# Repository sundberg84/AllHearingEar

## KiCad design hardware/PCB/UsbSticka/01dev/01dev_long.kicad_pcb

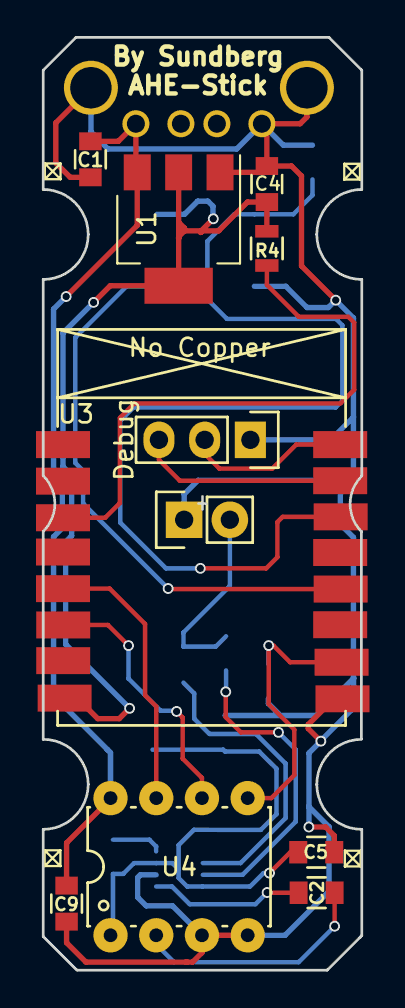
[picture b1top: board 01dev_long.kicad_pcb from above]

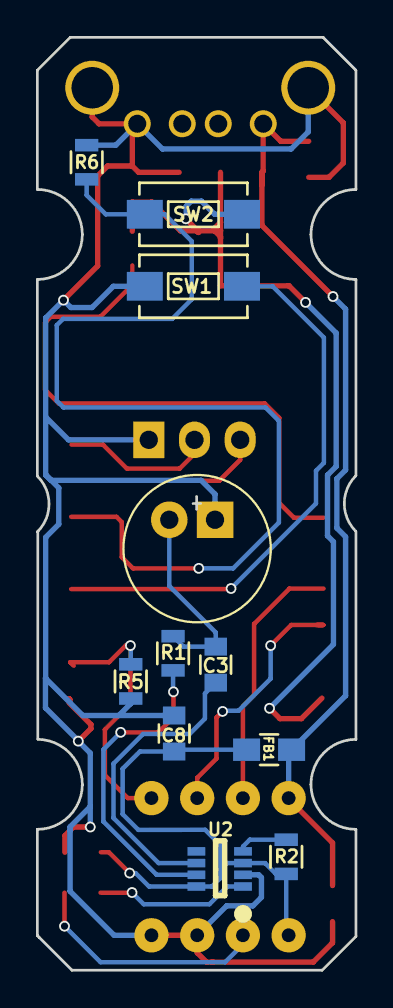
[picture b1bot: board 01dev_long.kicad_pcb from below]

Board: 2 copper layers, 17.7 x 51.8 mm, 22 parts (10 on the bottom side), 18 nets.

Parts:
C1, C2, C3, C5, C8, C9: 0,1; C_0805
C4: 10; C_0805
Debug: Debug; Socket_Strip_Straight_1x03
FB1: FERRITE; C_0805_HandSoldering
P1: USB_B; USB_A_AS
P2: MIC; Socket_Strip_Straight_1x02
R1, R2: 2,2k; R_0805
R4, R5, R6: 10k; R_0805
SW1, SW2: SW_PUSH; SW_SPST_EVQPE1
U1: LM1117-3.3; SOT-223
U2: MAX9813; SOT-23-8
U3: ESP-07v2; ESP-07_AS
U4: MCP3201; PDIP-8

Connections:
+5V: C1.1, C9.2, FB1.2, P1.1, U1.3, U4.8
ANALOG: C2.2, U4.2
GND: C1.2, C4.2, C5.1, C8.1, C9.1, Debug.1, P1.4, P1.5, P2.1, R5.2, R6.1, SW1.2, U1.1, U2.2, U3.9, U4.3, U4.4
MISO: U3.6, U4.6
unnamed: C2.1, U2.1
unnamed: C3.1, P2.2, R1.2
unnamed: C3.2, U2.6
unnamed: C5.2, C8.2, FB1.1, R2.1, U2.3, U2.8, U4.1
unnamed: Debug.2, U3.16
unnamed: Debug.3, U3.15
unnamed: R1.1, U2.7
unnamed: R2.2, U2.4
unnamed: R4.1, U3.3
unnamed: R6.2, SW2.1, U3.14
unnamed: SW1.1, U3.12
SCLK: U3.5, U4.7
SS: R5.1, U3.10, U4.5
VCC: C4.1, R4.2, SW2.2, U1.2, U1.4, U3.8

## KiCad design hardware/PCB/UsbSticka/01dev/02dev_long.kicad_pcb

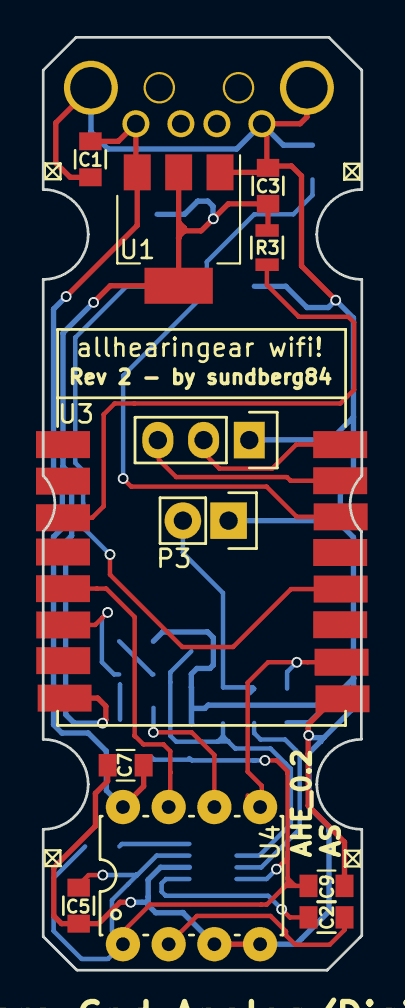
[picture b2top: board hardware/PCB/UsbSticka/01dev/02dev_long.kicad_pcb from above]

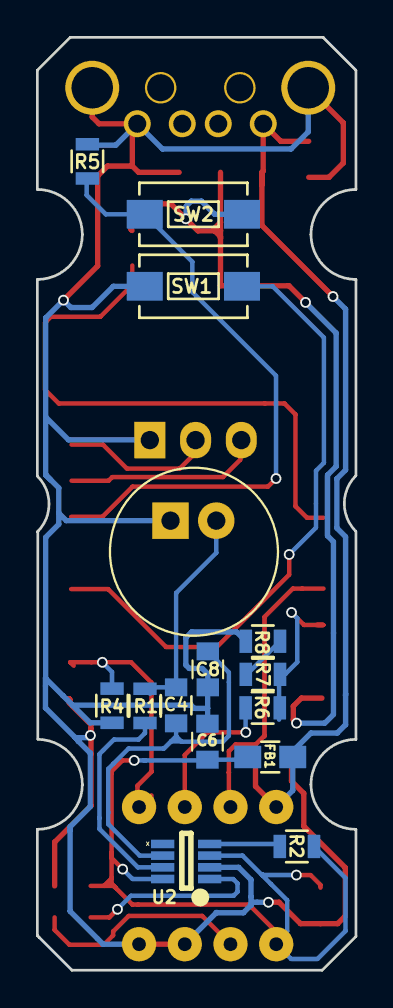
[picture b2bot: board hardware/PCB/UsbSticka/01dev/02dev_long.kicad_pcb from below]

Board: 2 copper layers, 17.7 x 51.8 mm, 27 parts (14 on the bottom side), 20 nets.

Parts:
C1, C2, C4, C5, C6, C7, C8: 0,1; C_0805
C3: 10; C_0805
C9: 10uF; C_0805
FB1: FERRITE; C_0805_HandSoldering
P1: USB_B; USB_A_AS
P2: MIC; Socket_Strip_Straight_1x02
P3: Debug; Socket_Strip_Straight_1x03
R1, R2: 2,2k; R_0805
R3, R4, R5: 10k; R_0805
R6, R7, R8: 1k; R_0805
SW1, SW2: SW_PUSH; SW_SPST_EVQPE1
U1: LM1117-3.3; SOT-223
U2: MAX9813; SOT-23-8
U3: ESP-07v2; ESP-07_AS
U4: MCP3201; PDIP-8

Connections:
+5V: C1.1, C7.2, FB1.2, P1.1, U1.3, U4.8
ANALOG: C2.1, U2.1
GND: C1.2, C3.2, C5.1, C6.1, C7.1, C8.1, C9.2, P1.4, P1.5, P2.1, P3.1, R4.2, R5.1, R8.2, SW1.2, U1.1, U2.2, U3.9, U4.3, U4.4
MISO: R6.1, R7.1, U3.6
unnamed: C2.2, U4.2
unnamed: C4.1, P2.2, R1.2
unnamed: C4.2, C8.2, U2.6
unnamed: C5.2, C6.2, C9.1, FB1.1, R2.1, U2.3, U2.8, U4.1
unnamed: P3.2, U3.16
unnamed: P3.3, U3.15
unnamed: R1.1, U2.7
unnamed: R2.2, U2.4
unnamed: R3.1, U3.3
unnamed: R5.2, SW2.1, U3.14
unnamed: R6.2, U4.6
unnamed: R7.2, R8.1
unnamed: SW1.1, U3.12
SCLK: U3.5, U4.7
SS: R4.1, U3.10, U4.5
VCC: C3.1, R3.2, SW2.2, U1.2, U1.4, U3.8

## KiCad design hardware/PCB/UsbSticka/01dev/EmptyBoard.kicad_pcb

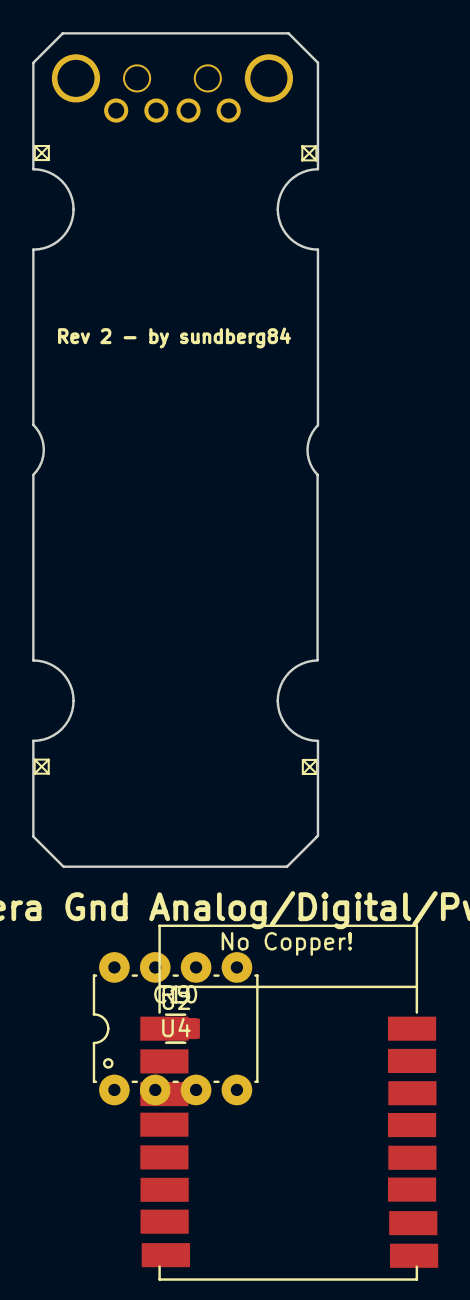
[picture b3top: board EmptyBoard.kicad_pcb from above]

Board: 2 copper layers, 17.7 x 51.8 mm, 5 parts (0 on the bottom side), 6 nets.

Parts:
C10: 0,1; C_0805
P1: USB_B; USB_A_AS
R9: 10k; R_0805
U2: ESP-07v2; ESP-07_AS
U4: MCP3201; PDIP-8

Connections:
GND: C10.1, P1.4, P1.5, R9.2, U2.9, U4.3, U4.4
MISO: U2.6, U4.6
unnamed: C10.2, U4.1
SCLK: U2.5, U4.7
SS: U2.10, U4.5
VCC: U2.8, U4.8

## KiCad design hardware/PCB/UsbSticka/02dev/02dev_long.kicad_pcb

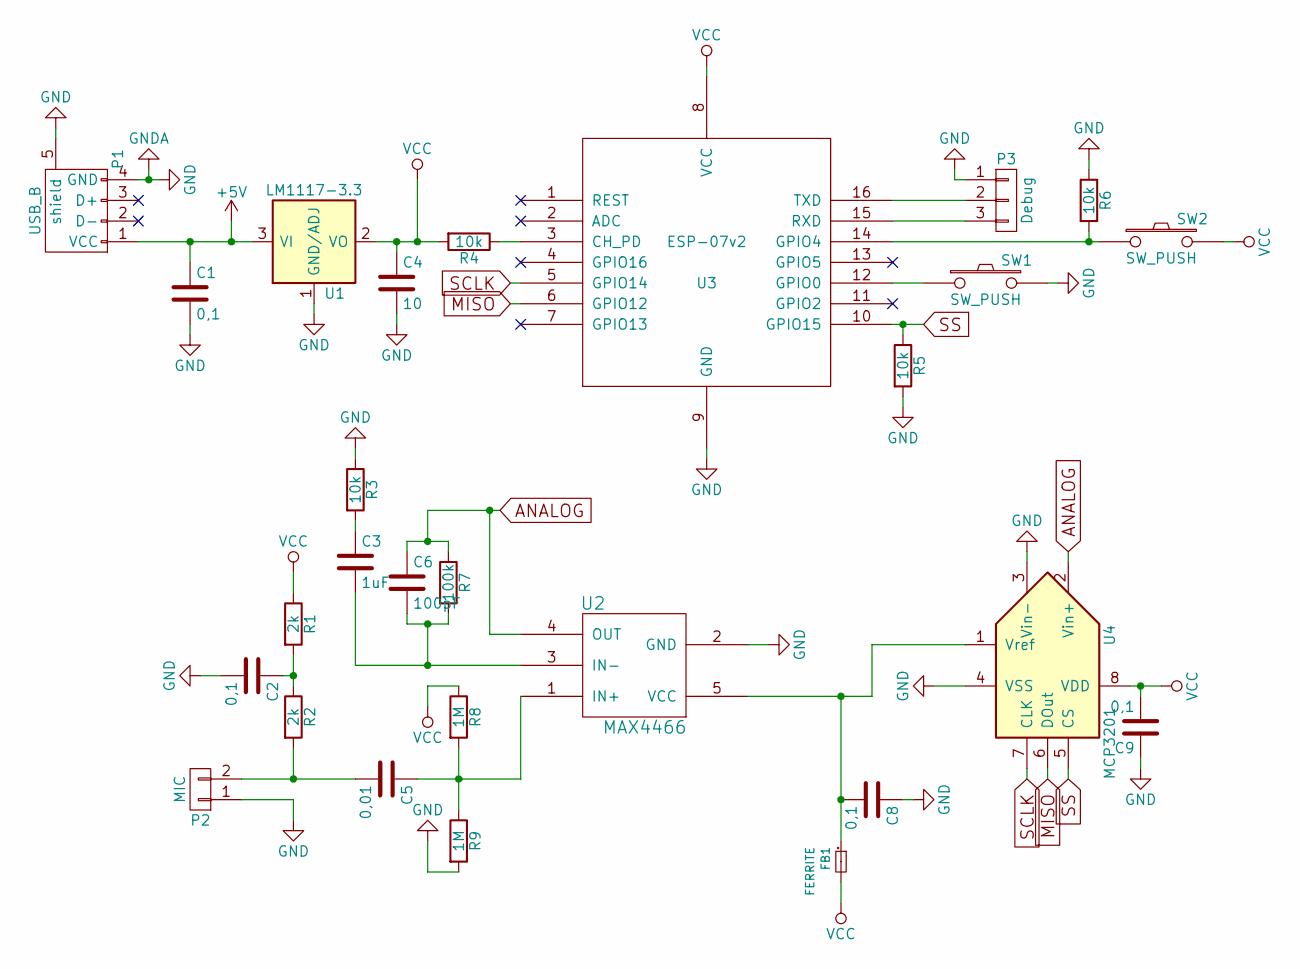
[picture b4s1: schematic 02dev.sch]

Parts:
C1, C2, C8, C9: 0,1; C_0805
C3: 1uF; C_0805
C4: 10; C_0805
C5: 0,01; C_0805
C6: 100pF; C_0805
FB1: FERRITE; C_0805_HandSoldering
P1: USB_B; USB_Micro-B
P2: MIC; Socket_Strip_Straight_1x02
P3: Debug; Socket_Strip_Straight_1x03
R1, R2: 2k; R_0805
R3, R4, R5, R6: 10k; R_0805
R7: 100k; R_0805
R8, R9: 1M; R_0805
SW1, SW2: SW_PUSH; SW_SPST_EVQPE1
U1: LM1117-3.3; SOT-223
U2: MAX4466; SC-70-5
U3: ESP-07v2; ESP-07_AS
U4: MCP3201; PDIP-8

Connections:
+5V: C1.1, P1.1 (VCC), U1.3 (VI)
ANALOG: C6.1, R7.1, U2.4 (OUT), U4.2 (Vin+)
GND: C1.2, C2.2, C4.2, C8.1, C9.1, P1.4 (GND), P1.5 (shield), P2.1, P3.1, R3.1, R5.2, R6.1, R9.2, SW1.2, U1.1 (GND/ADJ), U2.2 (GND), U3.9 (GND), U4.3 (Vin-), U4.4 (VSS)
MISO: U3.6 (GPIO12), U4.6 (DOut)
unnamed: C2.1, R1.2, R2.1
unnamed: C3.1, R3.2
unnamed: C3.2, C6.2, R7.2, U2.3 (IN-)
unnamed: C5.1, R8.2, R9.1, U2.1 (IN+)
unnamed: C5.2, P2.2, R2.2
unnamed: C8.2, FB1.1, U2.5 (VCC), U4.1 (Vref)
unnamed: P3.2, U3.16 (TXD)
unnamed: P3.3, U3.15 (RXD)
unnamed: R4.1, U3.3 (CH_PD)
unnamed: R6.2, SW2.1, U3.14 (GPIO4)
unnamed: SW1.1, U3.12 (GPIO0)
SCLK: U3.5 (GPIO14), U4.7 (CLK)
SS: R5.1, U3.10 (GPIO15), U4.5 (CS)
VCC: C4.1, C9.2, FB1.2, R1.1, R4.2, R8.1, SW2.2, U1.2 (VO), U1.4 (VO), U3.8 (VCC), U4.8 (VDD)

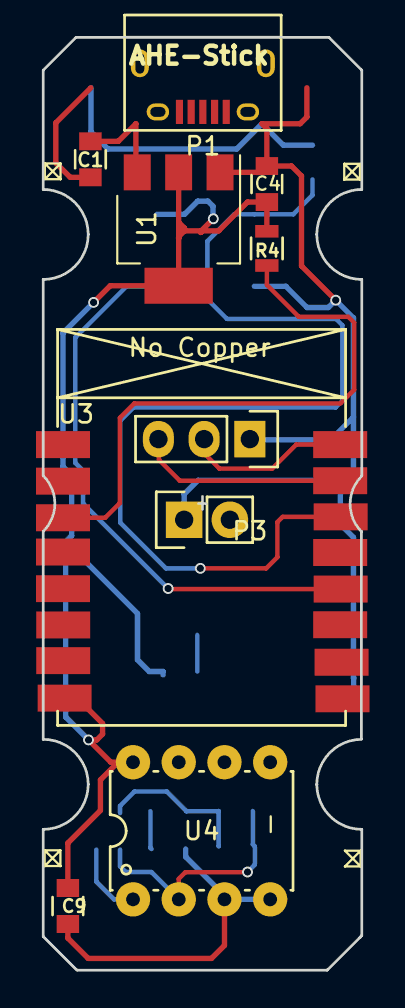
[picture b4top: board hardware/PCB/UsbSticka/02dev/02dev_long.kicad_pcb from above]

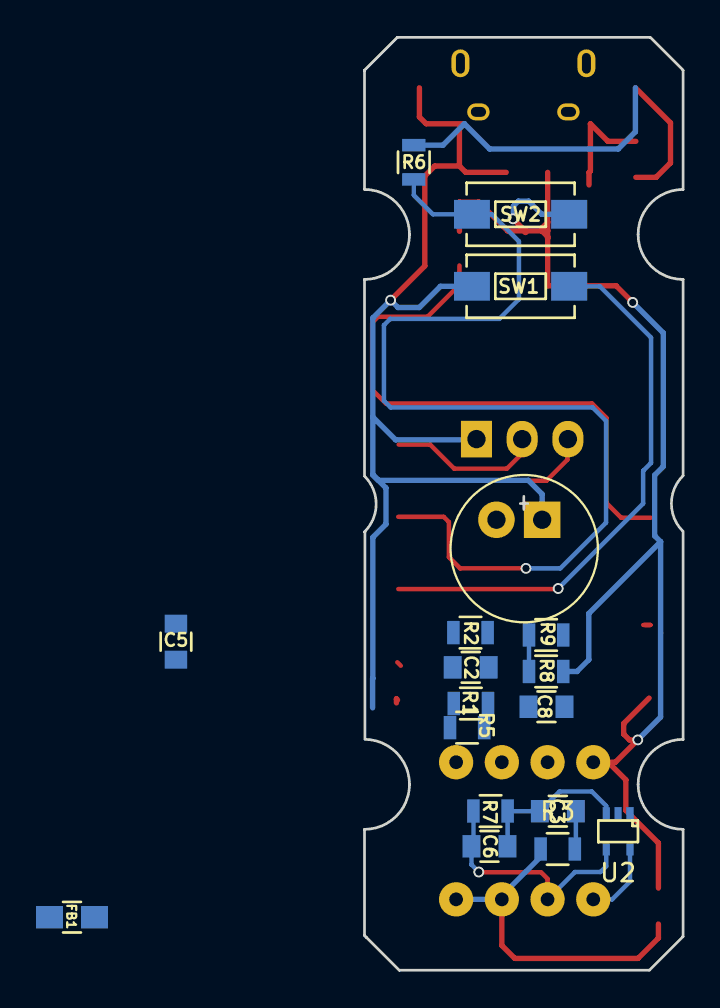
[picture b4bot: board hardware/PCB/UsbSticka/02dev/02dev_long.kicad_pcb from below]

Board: 2 copper layers, 17.7 x 51.8 mm, 27 parts (17 on the bottom side), 18 nets.

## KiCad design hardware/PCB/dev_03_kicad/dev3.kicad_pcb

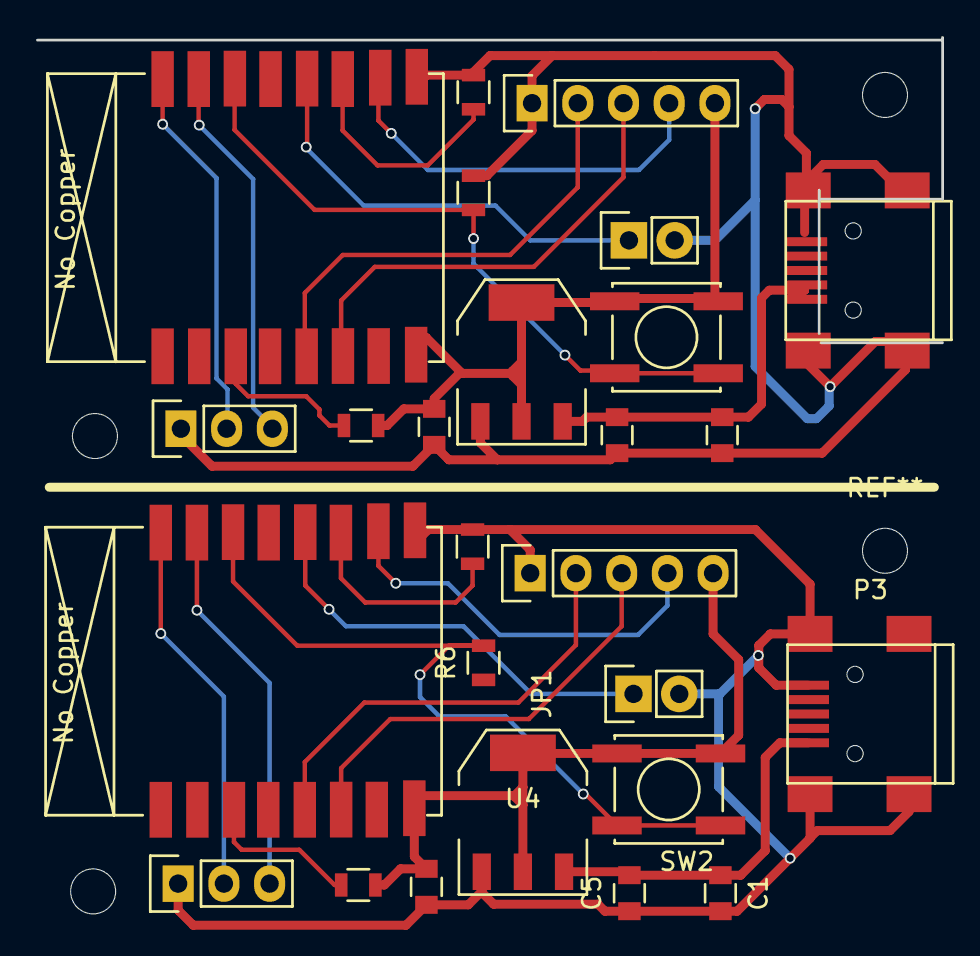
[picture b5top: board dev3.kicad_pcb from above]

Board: 2 copper layers, 7 parts (0 on the bottom side), 4 nets.

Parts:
C1: 0,1uF; C_0805
C5: 10uF; C_0805
JP1: JUMPER; Pin_Header_Straight_1x02
P3: USB_OTG; USB_Mini-B
R6: 10k; R_0805
SW2: SW_PUSH; SW_SPST_EVPBF
U4: LM1117-3.3; SOT-223

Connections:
+3.3VDAC: SW2.2, U4.2, U4.4
+5VD: C1.1, C5.2, P3.1, U4.3
GNDA: C1.2, C5.1, JP1.2, P3.5, P3.6, R6.1, U4.1
unnamed: R6.2, SW2.1
